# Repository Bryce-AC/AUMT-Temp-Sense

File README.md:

# AUMT Temp Sense
 Tyre temperature monitoring sensors/arduino projcet

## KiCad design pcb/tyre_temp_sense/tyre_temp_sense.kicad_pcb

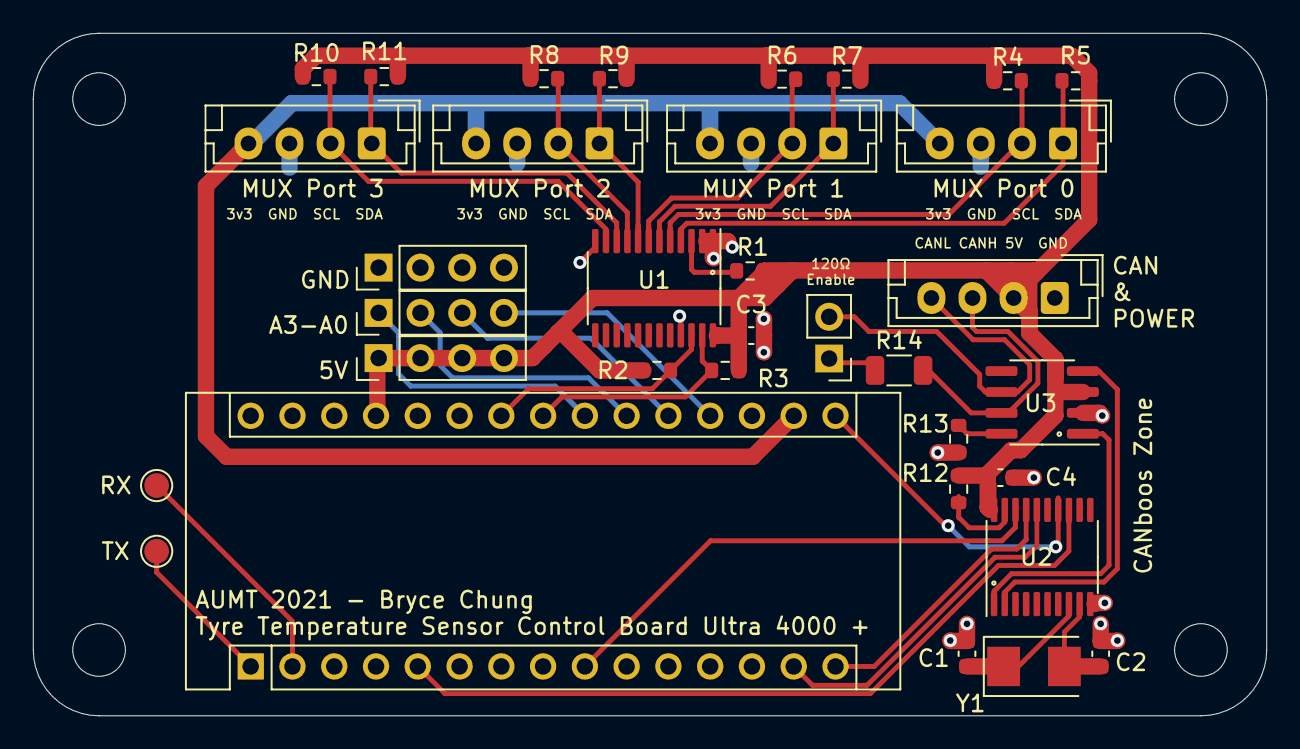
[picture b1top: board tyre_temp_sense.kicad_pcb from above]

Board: 2 copper layers, 75.0 x 41.5 mm, 34 parts (0 on the bottom side), 34 nets.

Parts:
A1: Arduino_Nano_v3.x; Arduino_Nano
C1, C2: 30pF; C_0603_1608Metric
C3: 10uF; C_0603_1608Metric
C4: 1uF; C_0603_1608Metric
J1: POWER & CAN; JST_EH_B4B-EH-A_1x04_P2.50mm_Vertical
J2: MUX Port 0; JST_EH_B4B-EH-A_1x04_P2.50mm_Vertical
J3: MUX Port 1; JST_EH_B4B-EH-A_1x04_P2.50mm_Vertical
J4: MUX Port 2; JST_EH_B4B-EH-A_1x04_P2.50mm_Vertical
J5: MUX Port 3; JST_EH_B4B-EH-A_1x04_P2.50mm_Vertical
J6: Conn_01x02; PinHeader_1x02_P2.54mm_Vertical
J7: A; PinHeader_1x04_P2.54mm_Vertical
J8, J9: GND; PinHeader_1x04_P2.54mm_Vertical
R1, R12, R13: 10K; R_0603_1608Metric
R2, R3, R4, R5, R6, R7, R8, R9, R10, R11: 4.7K; R_0603_1608Metric
R14: 120; R_1206_3216Metric
TP8: RX; TestPoint_Pad_D1.5mm
TP9: TX; TestPoint_Pad_D1.5mm
U1: TCA9548APWR; TSSOP-24_4.4x7.8mm_P0.65mm
U2: MCP2515-I/ST; TSSOP-20_4.4x6.5mm_P0.65mm
U3: MCP2551-I-SN; SOIC-8_3.9x4.9mm_P1.27mm
Y1: 8 mhz; Crystal_SMD_5032-2Pin_5.0x3.2mm

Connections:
+3V3: A1.17, J2.4, J3.4, J4.4, J5.4
+5V: A1.27, C3.2, C4.1, J1.2, J9.1, J9.2, J9.3, J9.4, R1.1, R2.1, R3.1, R4.1, R5.1, R6.1, R7.1, R8.1, R9.1, R10.1, R11.1, R12.1, U1.24, U2.20, U3.3
A0: A1.19, J7.4
A1: A1.20, J7.3
A2: A1.21, J7.2
A3: A1.22, J7.1
CAN+: J1.3, R14.2, U3.7
CAN-: J1.4, J6.2, U3.6
CLK_CAN: A1.16, U2.14
D2: A1.5, U2.13
D6: A1.9, U2.18
GND: A1.4, A1.29, C1.2, C2.2, C3.1, C4.2, J1.1, J2.3, J3.3, J4.3, J5.3, J8.1, J8.2, J8.3, J8.4, R13.2, U1.1, U1.2, U1.12, U1.21, U2.10, U3.2
MISO_CAN: A1.15, U2.17
MOSI_CAN: A1.14, U2.16
unnamed: A1.1, TP9.1
unnamed: A1.2, TP8.1
unnamed: C1.1, U2.8, Y1.1
unnamed: C2.1, U2.9, Y1.2
unnamed: J2.1, R5.2, U1.4
unnamed: J2.2, R4.2, U1.5
unnamed: J3.1, R7.2, U1.6
unnamed: J3.2, R6.2, U1.7
unnamed: J4.1, R9.2, U1.8
unnamed: J4.2, R8.2, U1.9
unnamed: J5.1, R11.2, U1.10
unnamed: J5.2, R10.2, U1.11
unnamed: J6.1, R14.1
unnamed: R1.2, U1.3
unnamed: R12.2, U2.19
unnamed: R13.1, U3.8
unnamed: U2.1, U3.1
unnamed: U2.2, U3.4
SCL: A1.24, R2.2, U1.22
SDA: A1.23, R3.2, U1.23

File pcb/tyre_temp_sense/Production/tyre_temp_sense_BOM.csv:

Comment,Designator,Footprint,LCSC
30pF,"C2,C3",0603,C22397
10uF,"C1,C4",0604,C19702
10k,"R1,R12",0605,C25804
10K,R13,0606,C25804
120,R14,0607,C22859
4.7k,"R2,R3,R4,R5,R6,R7,R8,R9,R10,R11",0608,C23162
TCA9548APWR,U1,TSSOP-24_4.4x7.8x0.65P,C130026
MCP2515-I/ST,U2,TSSOP-20_4.4x6.5x0.65P,C15193
MCP2551T-I/SN,U3,SOIC-8_3.9x4.9x1.27P,C49558
8 mhz,Y1,SMD-5032_2P,C115962

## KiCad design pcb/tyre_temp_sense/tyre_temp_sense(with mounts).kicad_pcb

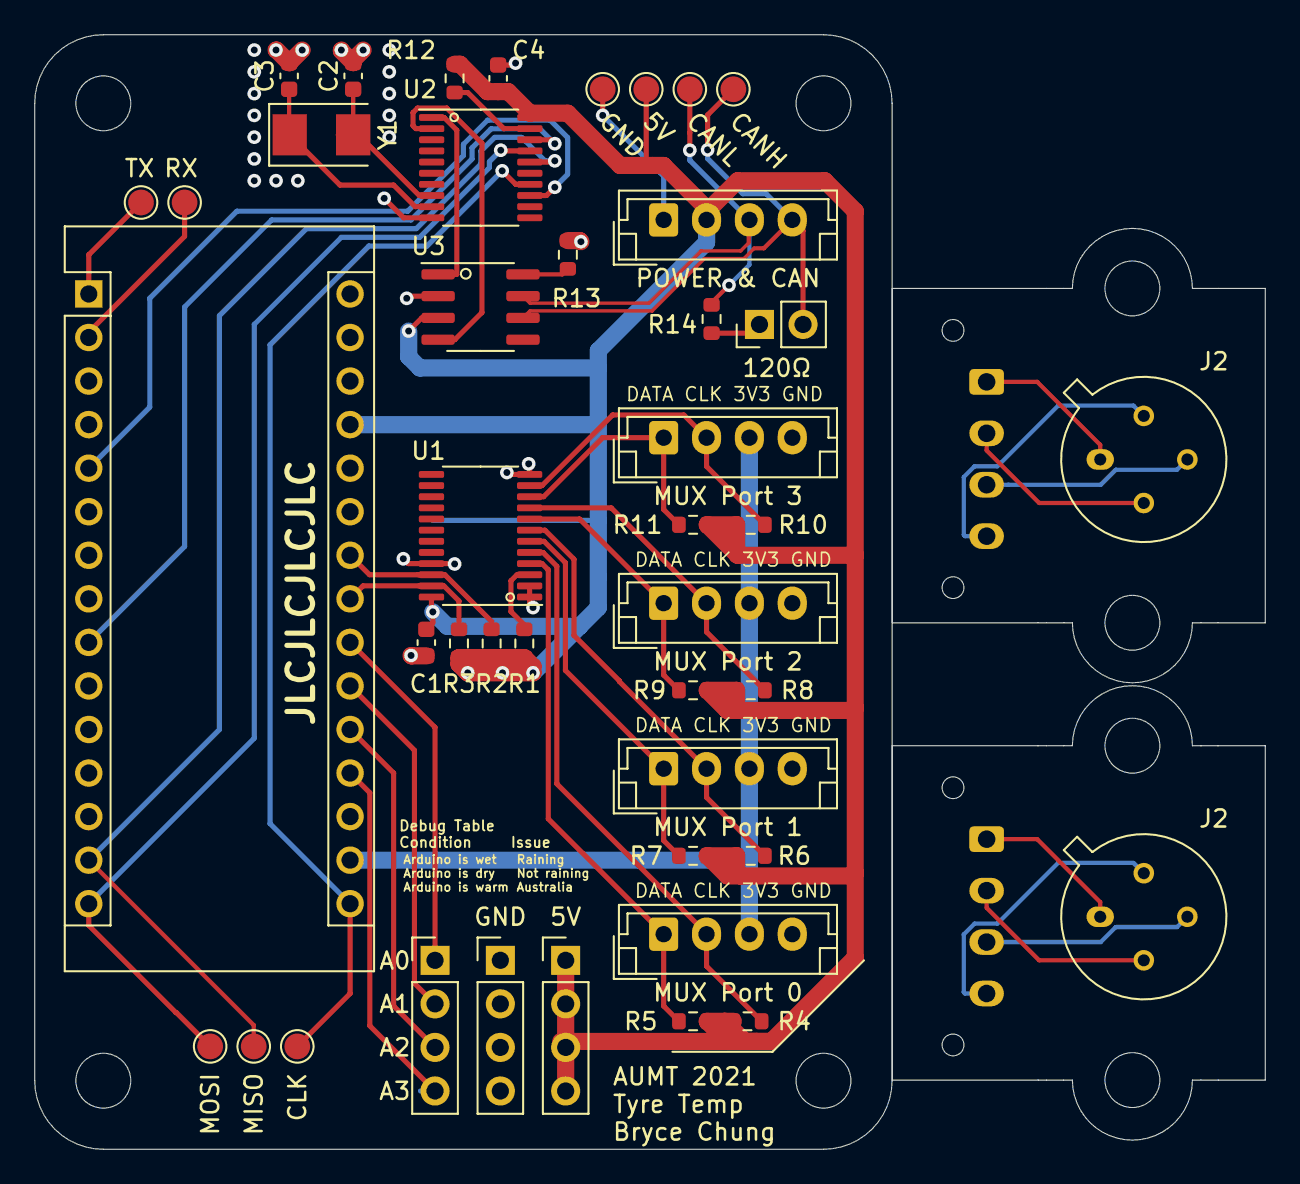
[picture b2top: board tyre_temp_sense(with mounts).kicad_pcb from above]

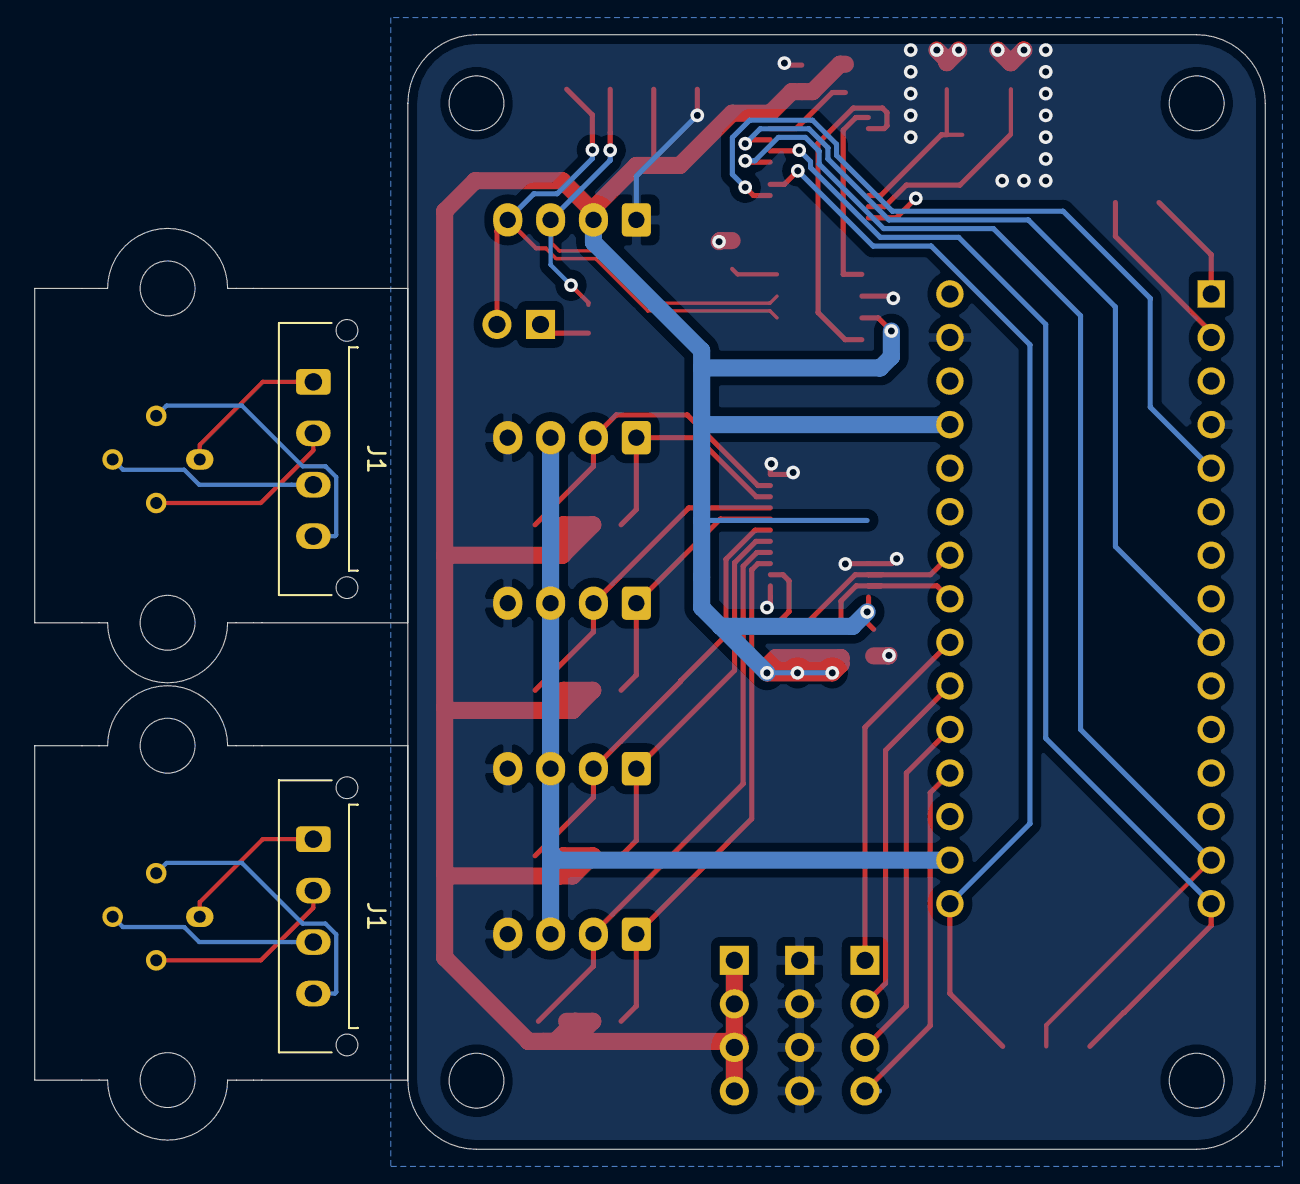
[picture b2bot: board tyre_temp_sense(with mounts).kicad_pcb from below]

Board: 2 copper layers, 71.8 x 65.0 mm, 45 parts (2 on the bottom side), 34 nets.

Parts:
A1: Arduino_Nano_v3.x; Arduino_Nano
C1, C4: 10uF; C_0603_1608Metric
C2, C3: 30pF; C_0603_1608Metric
J1, J1#2: Molex; Molex_Micro-Fit_3.0_43650-0415_1x04_P3.00mm_Vertical
J1#3: POWER & CAN; JST_EH_B4B-EH-A_1x04_P2.50mm_Vertical
J2, J2#2: MLX Sensor; TO-39-4_Window
J2#3: 5V; PinHeader_1x04_P2.54mm_Vertical
J3: Analog; PinHeader_1x04_P2.54mm_Vertical
J4: MUX Port 0; JST_EH_B4B-EH-A_1x04_P2.50mm_Vertical
J5: MUX Port 1; JST_EH_B4B-EH-A_1x04_P2.50mm_Vertical
J6: MUX Port 2; JST_EH_B4B-EH-A_1x04_P2.50mm_Vertical
J7: MUX Port 3; JST_EH_B4B-EH-A_1x04_P2.50mm_Vertical
J8: Conn_01x02; PinHeader_1x02_P2.54mm_Vertical
J9: GND; PinHeader_1x04_P2.54mm_Vertical
R1, R12: 10k; R_0603_1608Metric
R2, R3, R4, R5, R6, R7, R8, R9, R10, R11: 4.7k; R_0603_1608Metric
R13: 10K; R_0603_1608Metric
R14: 120; R_0603_1608Metric
TP1: CAN+; TestPoint_Pad_D1.5mm
TP2: GND; TestPoint_Pad_D1.5mm
TP3: CAN-; TestPoint_Pad_D1.5mm
TP4: 5V; TestPoint_Pad_D1.5mm
TP5: MOSI; TestPoint_Pad_D1.5mm
TP6: MISO; TestPoint_Pad_D1.5mm
TP7: CLK; TestPoint_Pad_D1.5mm
TP8: RX; TestPoint_Pad_D1.5mm
TP9: TX; TestPoint_Pad_D1.5mm
U1: TCA9548APWR; TSSOP-24_4.4x7.8mm_P0.65mm
U2: MCP2515-I/ST; TSSOP-20_4.4x6.5mm_P0.65mm
U3: MCP2551-I-SN; SOIC-8_3.9x4.9mm_P1.27mm
Y1: 8 mhz; Crystal_SMD_5032-2Pin_5.0x3.2mm

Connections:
+3V3: A1.17, J4.3, J5.3, J6.3, J7.3
+5V: A1.27, C1.2, C4.1, J1#3.2, J2#3.1, J2#3.2, J2#3.3, J2#3.4, R1.1, R2.1, R3.1, R4.1, R5.1, R6.1, R7.1, R8.1, R9.1, R10.1, R11.1, R12.1, TP4.1, U1.24, U2.20, U3.3
A0: A1.19, J3.4
A1: A1.20, J3.3
A2: A1.21, J3.2
A3: A1.22, J3.1
CAN+: J1#3.3, R14.2, TP3.1, U3.7
CAN-: J1#3.4, J8.2, TP1.1, U3.6
CLK_CAN: A1.16, TP7.1, U2.14
D2: A1.5, U2.13
D6: A1.9, U2.18
GND: A1.4, A1.29, C1.1, C2.2, C3.2, C4.2, J1#3.1, J4.4, J5.4, J6.4, J7.4, J9.1, J9.2, J9.3, J9.4, R13.2, TP2.1, U1.1, U1.2, U1.12, U1.21, U2.10, U3.2
MISO_CAN: A1.15, TP6.1, U2.17
MOSI_CAN: A1.14, TP5.1, U2.16
unnamed: A1.1, TP9.1
unnamed: A1.2, TP8.1
unnamed: C2.1, U2.8, Y1.2
unnamed: C3.1, U2.9, Y1.1
unnamed: J4.1, R5.2, U1.4
unnamed: J4.2, R4.2, U1.5
unnamed: J5.1, R7.2, U1.6
unnamed: J5.2, R6.2, U1.7
unnamed: J6.1, R9.2, U1.8
unnamed: J6.2, R8.2, U1.9
unnamed: J7.1, R11.2, U1.10
unnamed: J7.2, R10.2, U1.11
unnamed: J8.1, R14.1
unnamed: R1.2, U1.3
unnamed: R12.2, U2.19
unnamed: R13.1, U3.8
unnamed: U2.1, U3.1
unnamed: U2.2, U3.4
SCL: A1.24, R2.2, U1.22
SDA: A1.23, R3.2, U1.23

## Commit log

2021-07-14 Added project files
2021-07-15 Removed garbage
2021-07-19 Added sensor methods
    get_temp and print_temp
    both take a mux port and array pointer
2021-07-28 Schematic complete, starting PCB
2021-07-30 PCB design complete
2021-07-30 First revision, ready for production
    Added JLCPCB parts
2021-07-31 rev 1
2021-07-31 First revision, ready for production
    Added JLCPCB parts
    rev 1
    Revert "rev 1"
    This reverts commit d7fe8d90d780ed24d08af68c791964fcba5617af.
    Revert "Revert "rev 1""
    This reverts commit 5d4b21aec522fc29a8afe0da54f0448a4a3d7d19.
2021-07-31 Revert "rev 1"
    This reverts commit d7fe8d90d780ed24d08af68c791964fcba5617af.
2021-07-31 revision 2
2021-07-31 Second revision
2021-07-31 Added LCSC Part info
2021-08-01 Gerbers, drill, BOM and part pos added
2021-08-03 Added test code
    Can send the temp sensor data directly to dash
2021-08-30 code dump
    breadboard sandpit included for fixing the data weird data transmission
2021-09-01 added drivers and float code
2021-09-30 added column averaging
